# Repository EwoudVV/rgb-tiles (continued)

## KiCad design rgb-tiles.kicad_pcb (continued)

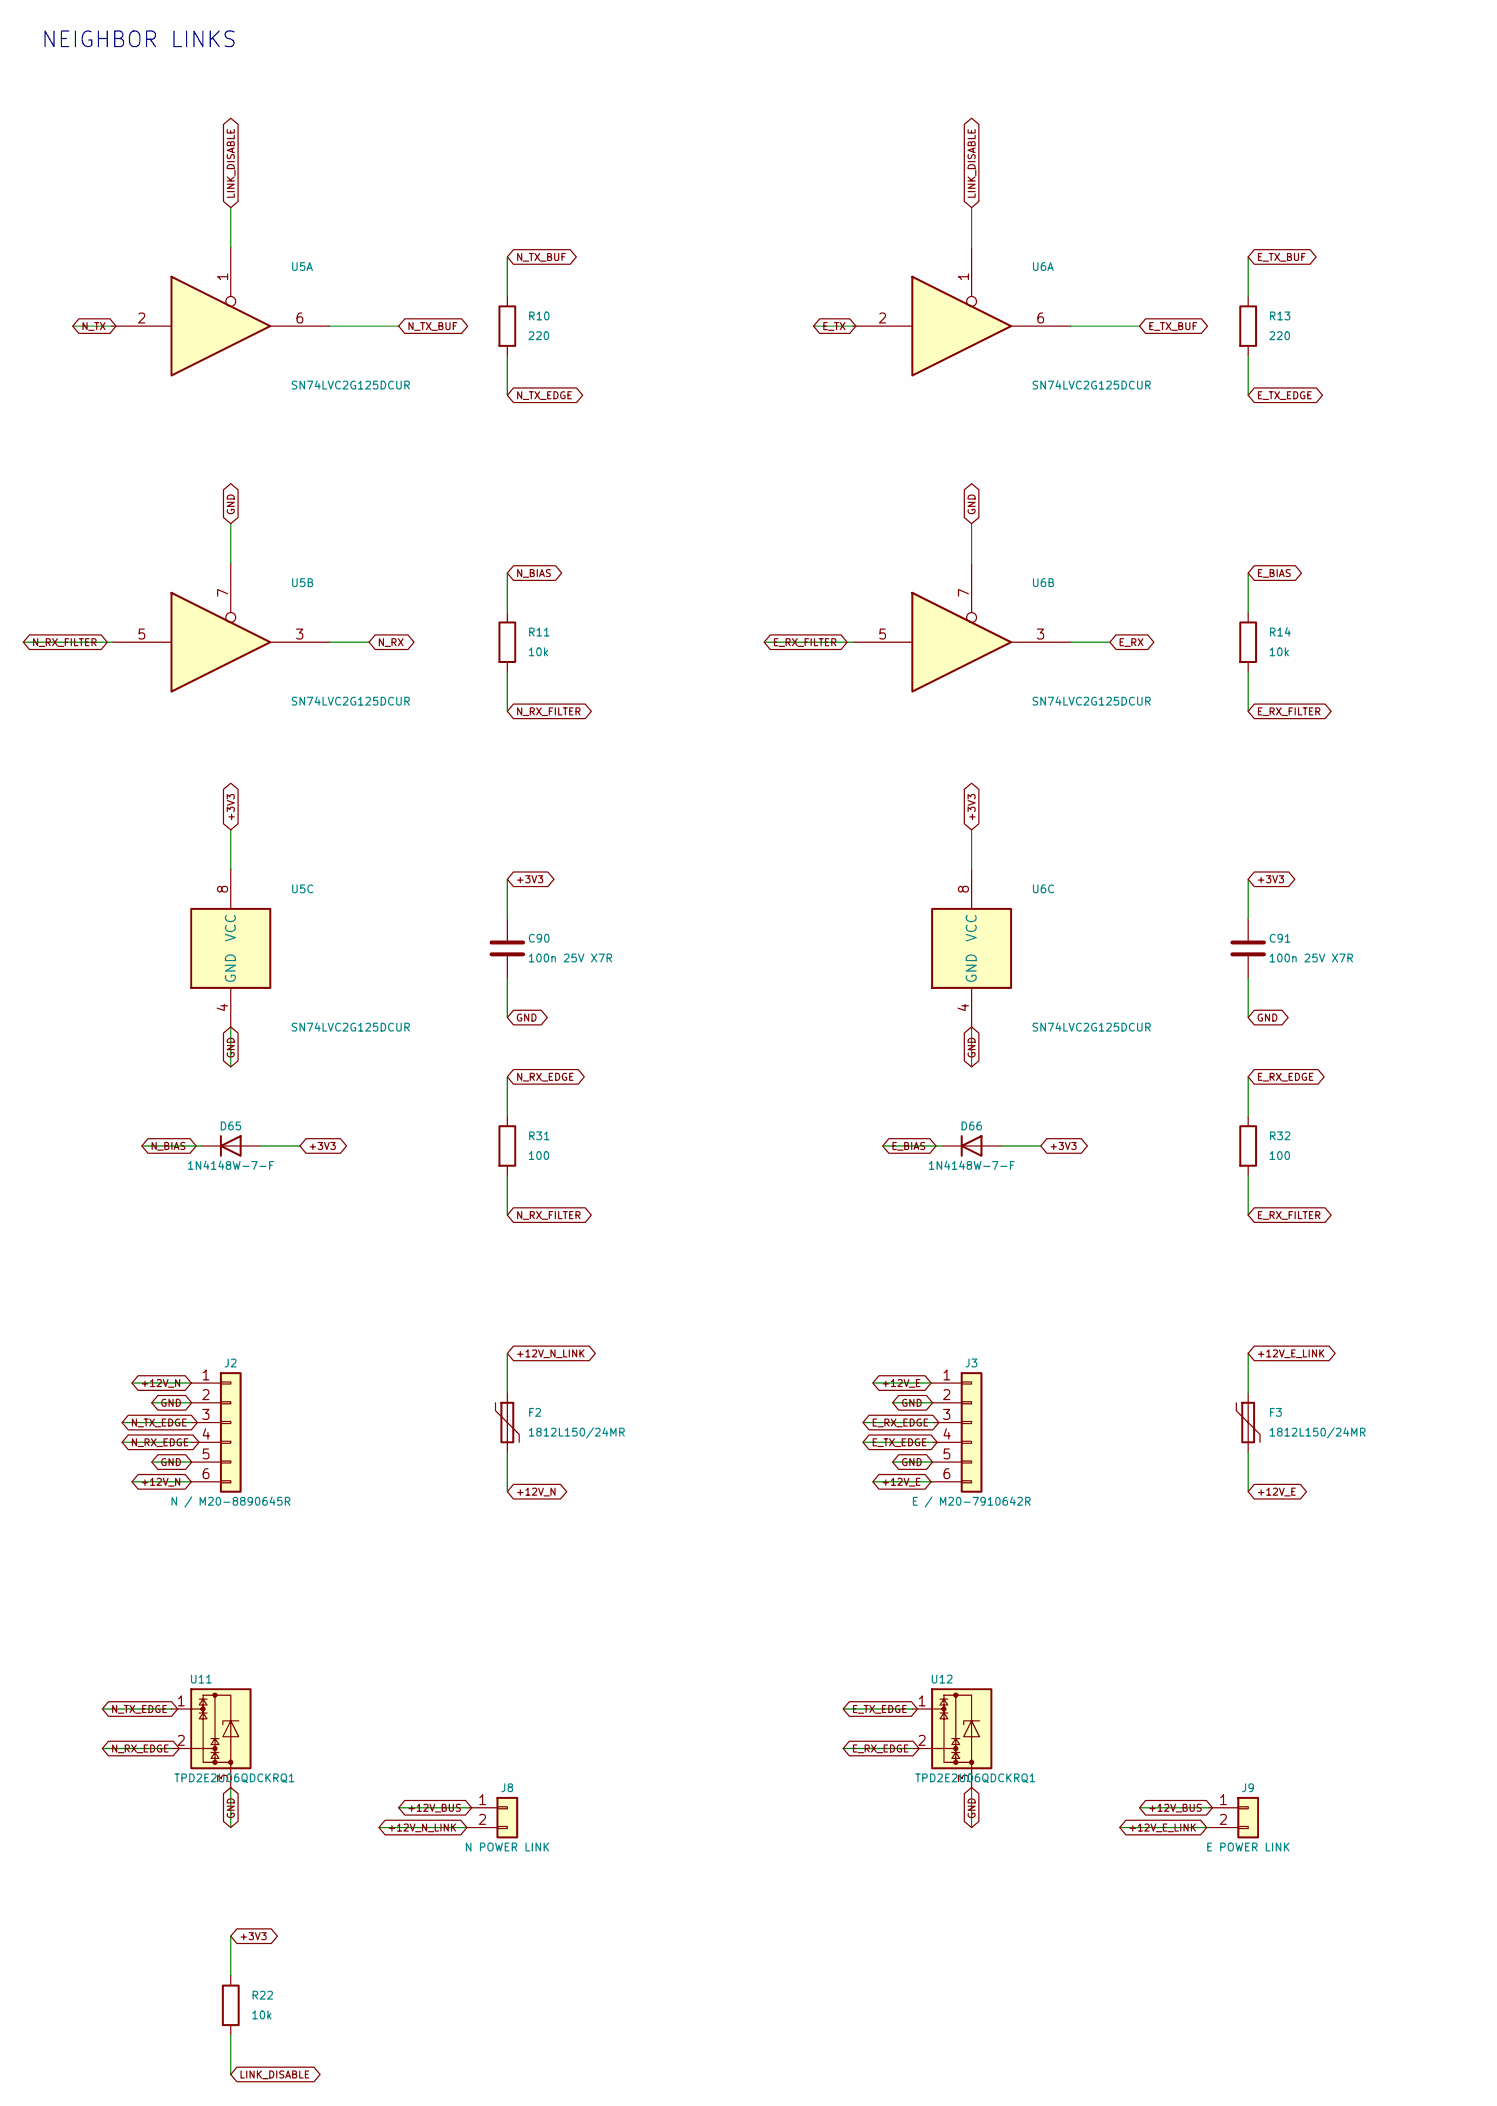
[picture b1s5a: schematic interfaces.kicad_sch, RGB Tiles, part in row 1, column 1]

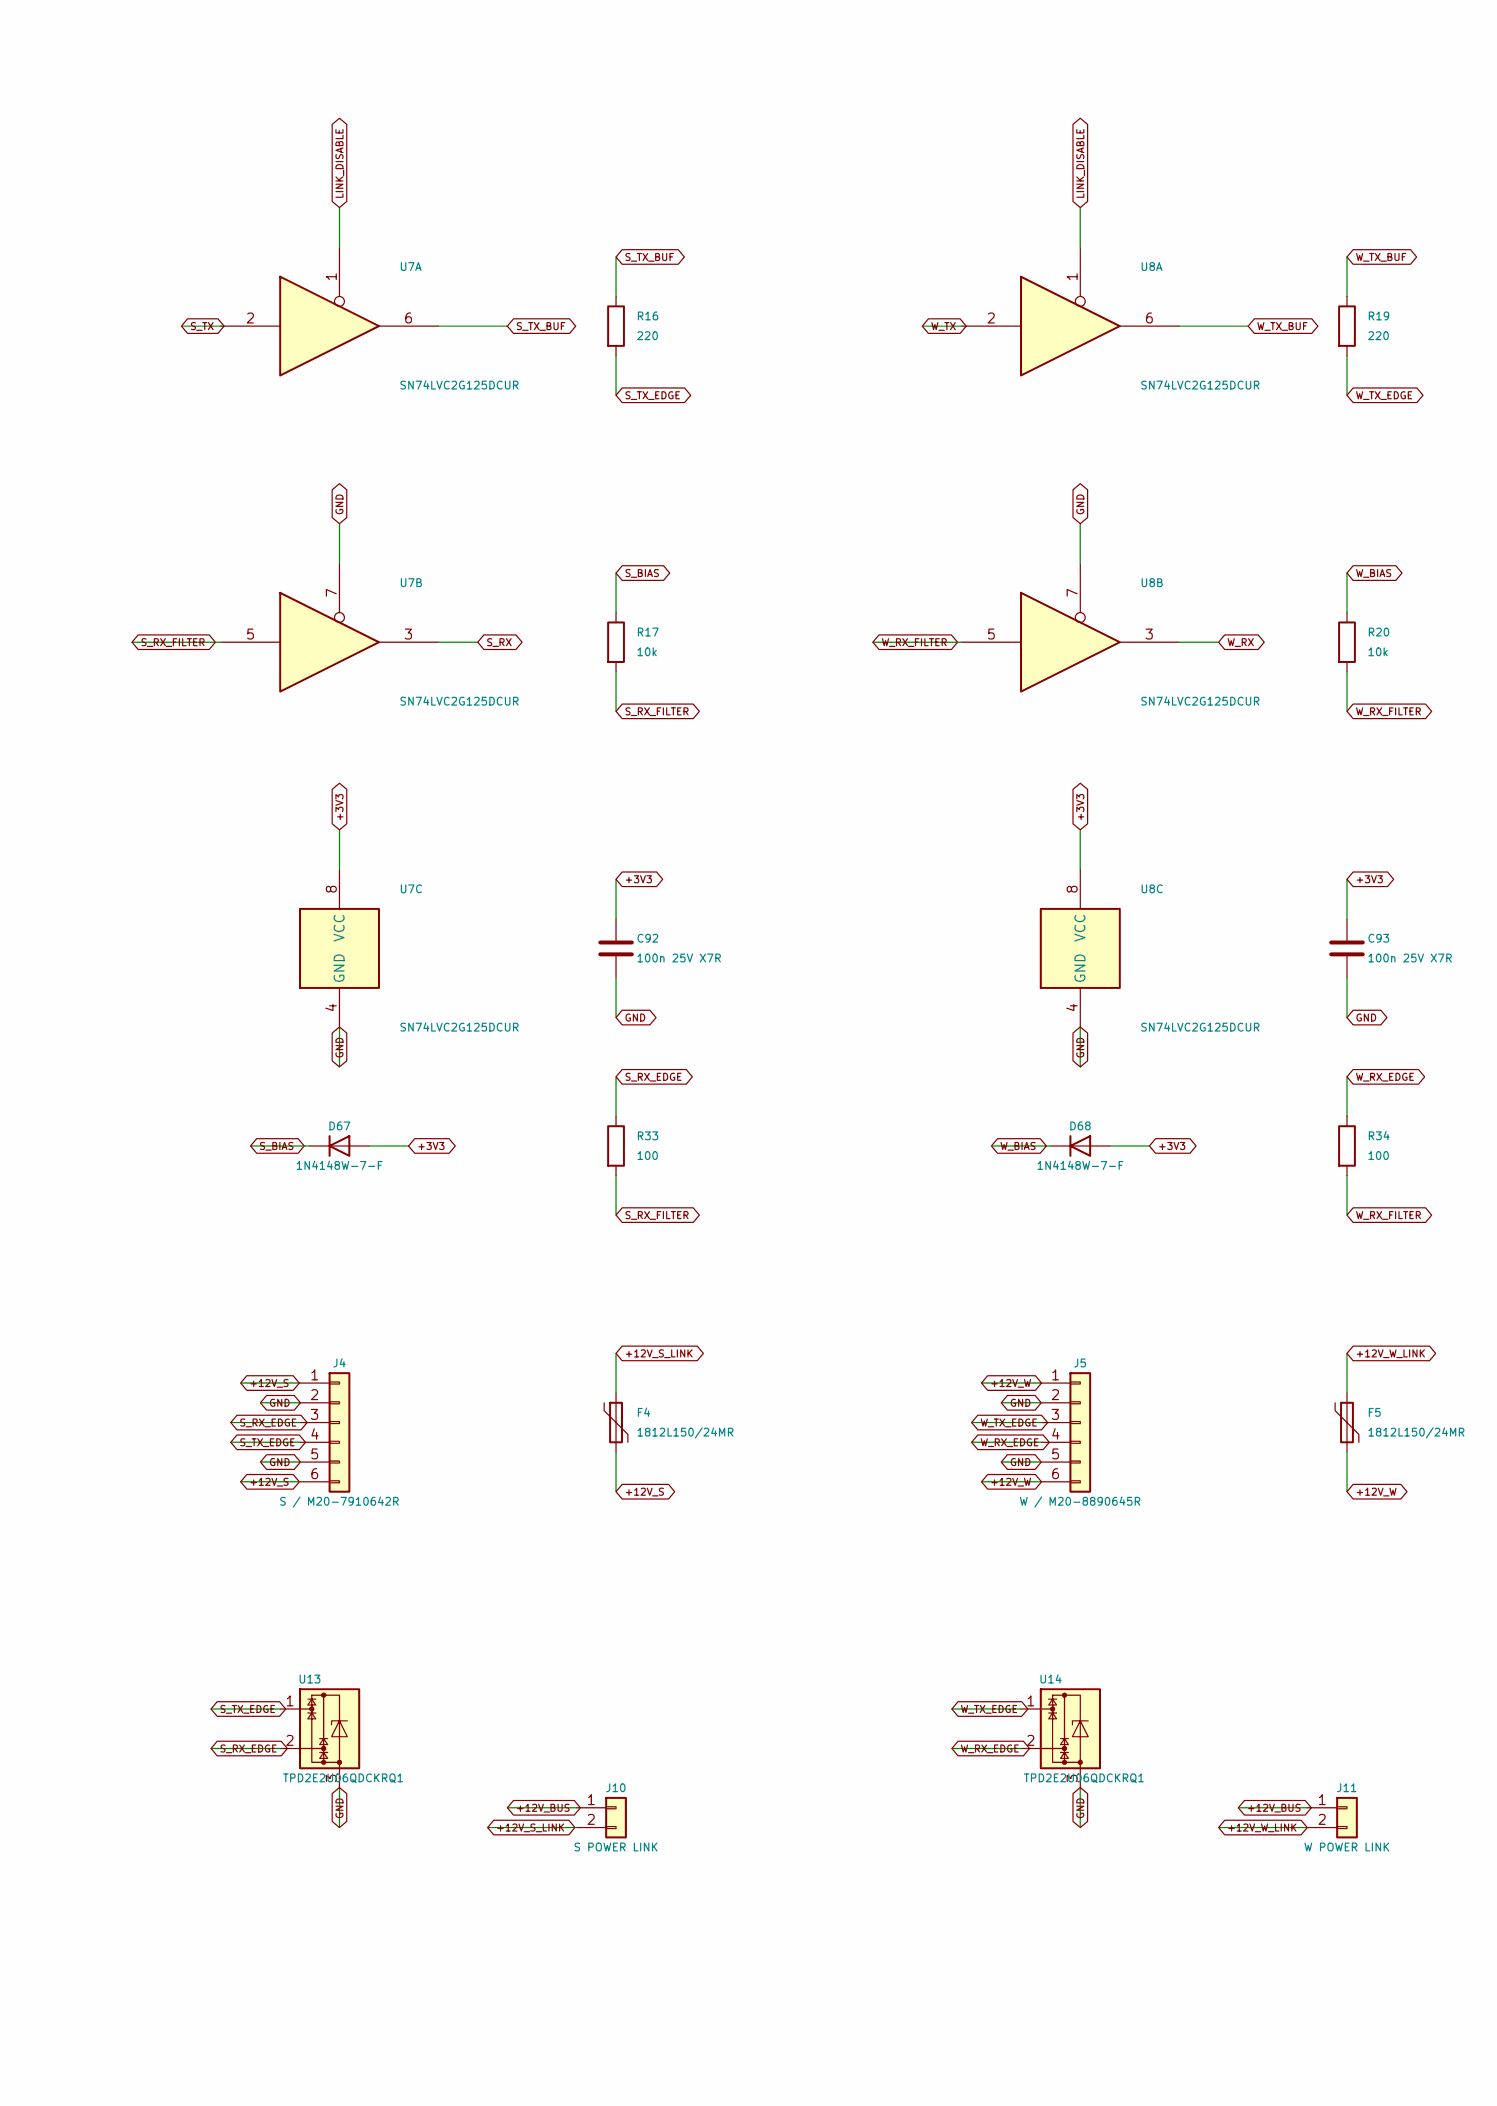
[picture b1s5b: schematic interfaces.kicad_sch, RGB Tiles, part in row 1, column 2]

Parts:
C90, C91, C92, C93: 100n 25V X7R; C_0603_1608Metric; MPN CL10B104KA8NNNC
D65, D66, D67, D68: 1N4148W-7-F; D_SOD-123; MPN 1N4148W-7-F
F2, F3, F4, F5: 1812L150/24MR; Fuse_1812_4532Metric; MPN 1812L150/24MR
J2: N / M20-8890645R; Harwin_M20-8890645R_1x06_RA_SMD; MPN M20-8890645R
J3: E / M20-7910642R; Harwin_M20-7910642R_1x06_RA_SMD; MPN M20-7910642R
J4: S / M20-7910642R; Harwin_M20-7910642R_1x06_RA_SMD; MPN M20-7910642R
J5: W / M20-8890645R; Harwin_M20-8890645R_1x06_RA_SMD; MPN M20-8890645R
J8: N POWER LINK; PinHeader_1x02_P2.54mm_Vertical; MPN A2541WV-2P
J9: E POWER LINK; PinHeader_1x02_P2.54mm_Vertical; MPN A2541WV-2P
J10: S POWER LINK; PinHeader_1x02_P2.54mm_Vertical; MPN A2541WV-2P
J11: W POWER LINK; PinHeader_1x02_P2.54mm_Vertical; MPN A2541WV-2P
R10, R13, R16, R19: 220; R_0603_1608Metric; Tolerance 1%; MPN RC0603FR-07220RL
R11, R14, R17, R20, R22: 10k; R_0603_1608Metric; Tolerance 1%; MPN RC0603FR-0710KL
R31, R32, R33, R34: 100; R_0603_1608Metric; Tolerance 1%; MPN RC0603FR-07100RL
U5, U6, U7, U8: SN74LVC2G125DCUR; VSSOP-8_2.3x2mm_P0.5mm; MPN SN74LVC2G125DCUR
U11, U12, U13, U14: TPD2E2U06QDCKRQ1; SOT-323_SC-70; MPN TPD2E2U06QDCKRQ1

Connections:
+3V3: C90.1, C91.1, C92.1, C93.1, D65.2 (A), D66.2 (A), D67.2 (A), D68.2 (A), R22.1, U5.8 (VCC), U6.8 (VCC), U7.8 (VCC), U8.8 (VCC); also elsewhere on the board
+12V_BUS: J8.1, J9.1, J10.1, J11.1; also elsewhere on the board
+12V_E: F3.2, J3.1, J3.6
+12V_E_LINK: F3.1, J9.2
+12V_N: F2.2, J2.1, J2.6
+12V_N_LINK: F2.1, J8.2
+12V_S: F4.2, J4.1, J4.6
+12V_S_LINK: F4.1, J10.2
+12V_W: F5.2, J5.1, J5.6
+12V_W_LINK: F5.1, J11.2
E_BIAS: D66.1 (K), R14.1
E_RX: U6.3; also elsewhere on the board
E_RX_EDGE: J3.3, R32.1, U12.2
E_RX_FILTER: R14.2, R32.2, U6.5
E_TX: U6.2; also elsewhere on the board
E_TX_BUF: R13.1, U6.6
E_TX_EDGE: J3.4, R13.2, U12.1
GND: C90.2, C91.2, C92.2, C93.2, J2.2, J2.5, J3.2, J3.5, J4.2, J4.5, J5.2, J5.5, U5.4 (GND), U5.7, U6.4 (GND), U6.7, U7.4 (GND), U7.7, U8.4 (GND), U8.7, U11.3, U12.3, U13.3, U14.3; also elsewhere on the board
LINK_DISABLE: R22.2, U5.1, U6.1, U7.1, U8.1; also elsewhere on the board
N_BIAS: D65.1 (K), R11.1
N_RX: U5.3; also elsewhere on the board
N_RX_EDGE: J2.4, R31.1, U11.2
N_RX_FILTER: R11.2, R31.2, U5.5
N_TX: U5.2; also elsewhere on the board
N_TX_BUF: R10.1, U5.6
N_TX_EDGE: J2.3, R10.2, U11.1
S_BIAS: D67.1 (K), R17.1
S_RX: U7.3; also elsewhere on the board
S_RX_EDGE: J4.3, R33.1, U13.2
S_RX_FILTER: R17.2, R33.2, U7.5
S_TX: U7.2; also elsewhere on the board
S_TX_BUF: R16.1, U7.6
S_TX_EDGE: J4.4, R16.2, U13.1
W_BIAS: D68.1 (K), R20.1
W_RX: U8.3; also elsewhere on the board
W_RX_EDGE: J5.4, R34.1, U14.2
W_RX_FILTER: R20.2, R34.2, U8.5
W_TX: U8.2; also elsewhere on the board
W_TX_BUF: R19.1, U8.6
W_TX_EDGE: J5.3, R19.2, U14.1

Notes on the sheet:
NEIGHBOR LINKS

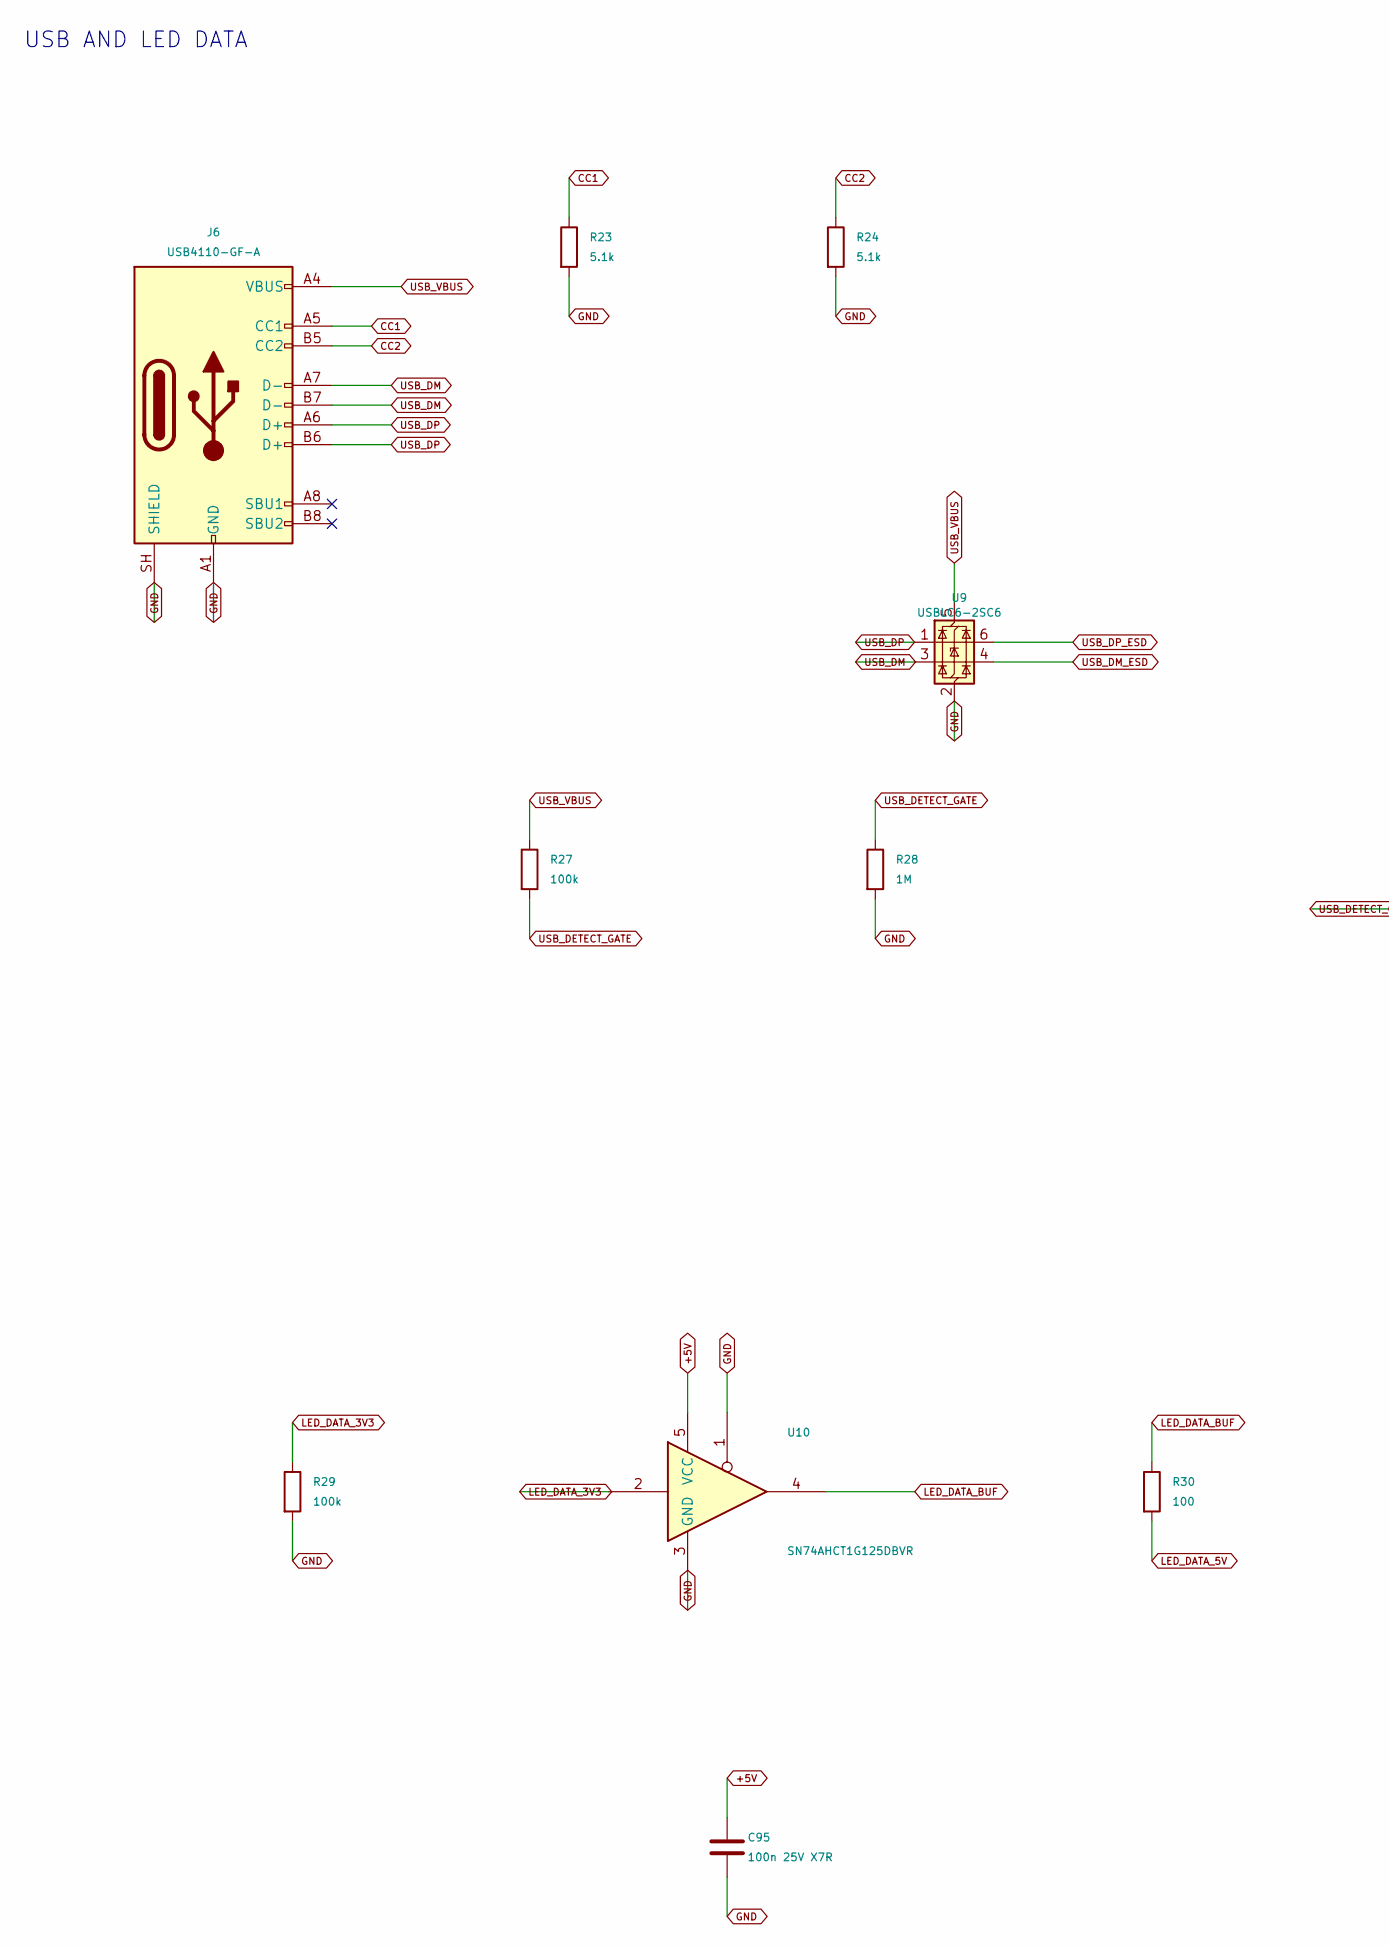
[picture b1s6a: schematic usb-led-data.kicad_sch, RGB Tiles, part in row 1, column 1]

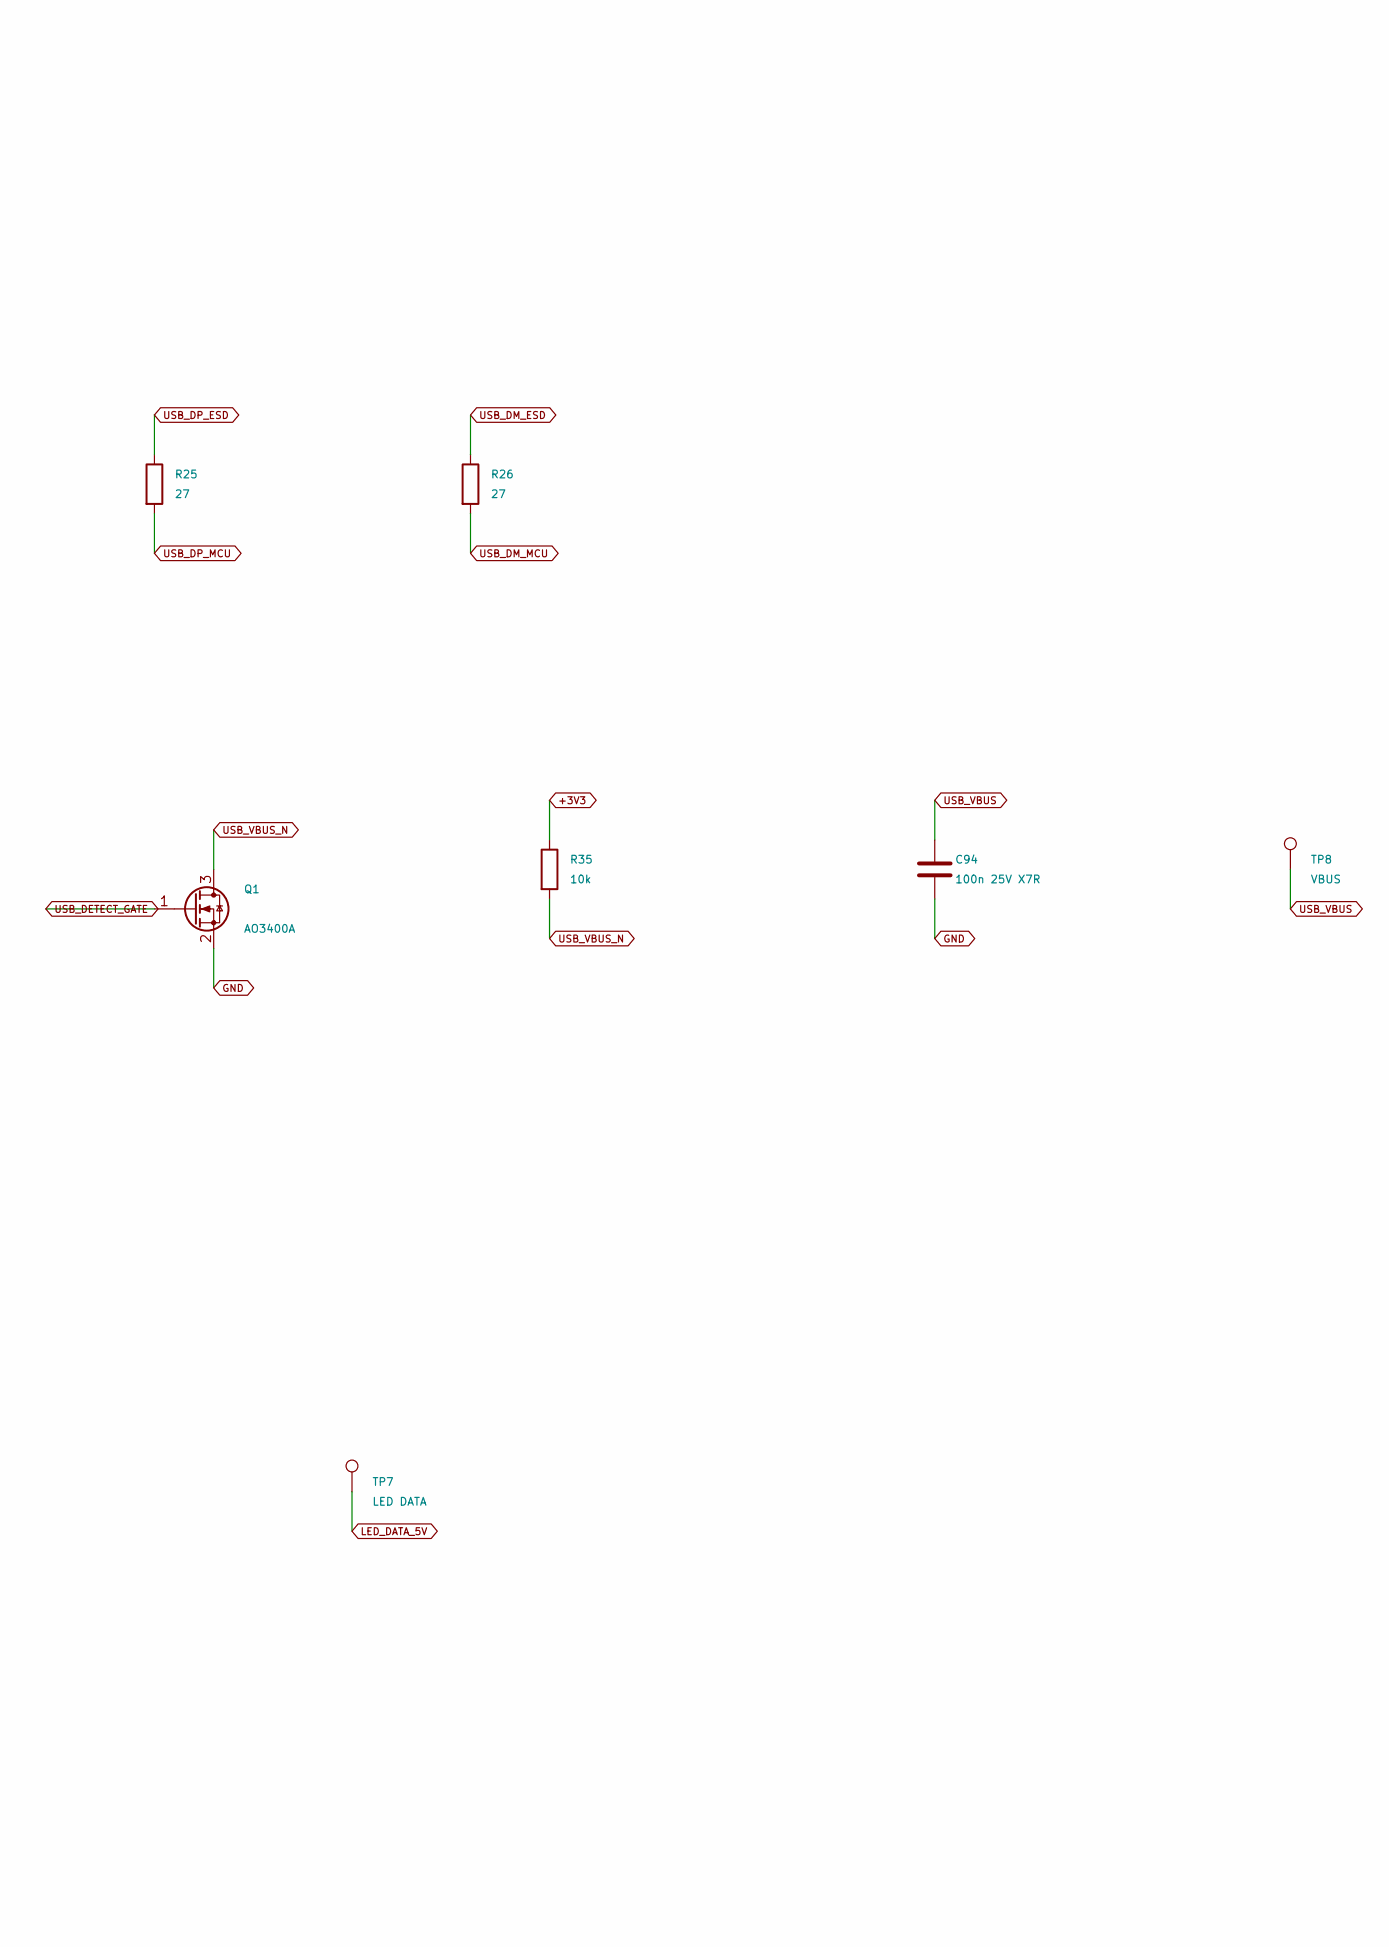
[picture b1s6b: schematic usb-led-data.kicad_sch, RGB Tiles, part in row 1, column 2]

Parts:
C94, C95: 100n 25V X7R; C_0603_1608Metric; MPN CL10B104KA8NNNC
J6: USB4110-GF-A; USB_C_Receptacle_GCT_USB4110; MPN USB4110-GF-A
Q1: AO3400A; SOT-23; MPN AO3400A
R23, R24: 5.1k; R_0603_1608Metric; Tolerance 1%; MPN RC0603FR-075K1L
R25, R26: 27; R_0603_1608Metric; Tolerance 1%; MPN RC0603FR-0727RL
R27, R29: 100k; R_0603_1608Metric; Tolerance 1%; MPN RC0603FR-07100KL
R28: 1M; R_0603_1608Metric; Tolerance 1%; MPN RC0603FR-071ML
R30: 100; R_0603_1608Metric; Tolerance 1%; MPN RC0603FR-07100RL
R35: 10k; R_0603_1608Metric; Tolerance 1%; MPN RC0603FR-0710KL
TP7: LED DATA; TestPoint_Pad_D1.5mm
TP8: VBUS; TestPoint_Pad_D1.5mm
U9: USBLC6-2SC6; SOT-23-6; MPN USBLC6-2SC6
U10: SN74AHCT1G125DBVR; SOT-23-5; MPN SN74AHCT1G125DBVR

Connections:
+3V3: R35.1; also elsewhere on the board
+5V: C95.1, U10.5 (VCC); also elsewhere on the board
CC1: J6.A5 (CC1), R23.1
CC2: J6.B5 (CC2), R24.1
GND: C94.2, C95.2, J6.A1 (GND), J6.A12 (GND), J6.B1 (GND), J6.B12 (GND), J6.SH (SHIELD), Q1.2 (S), R23.2, R24.2, R28.2, R29.2, U9.2 (GND), U10.1, U10.3 (GND); also elsewhere on the board
LED_DATA_3V3: R29.1, U10.2; also elsewhere on the board
LED_DATA_5V: R30.2, TP7.1; also elsewhere on the board
LED_DATA_BUF: R30.1, U10.4
USB_DETECT_GATE: Q1.1 (G), R27.2, R28.1
USB_DM: J6.A7 (D-), J6.B7 (D-), U9.3 (I/O2)
USB_DM_ESD: R26.1, U9.4 (I/O2)
USB_DM_MCU: R26.2; also elsewhere on the board
USB_DP: J6.A6 (D+), J6.B6 (D+), U9.1 (I/O1)
USB_DP_ESD: R25.1, U9.6 (I/O1)
USB_DP_MCU: R25.2; also elsewhere on the board
USB_VBUS: C94.1, J6.A4 (VBUS), J6.A9 (VBUS), J6.B4 (VBUS), J6.B9 (VBUS), R27.1, TP8.1, U9.5 (VBUS)
USB_VBUS_N: Q1.3 (D), R35.2; also elsewhere on the board

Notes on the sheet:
USB AND LED DATA

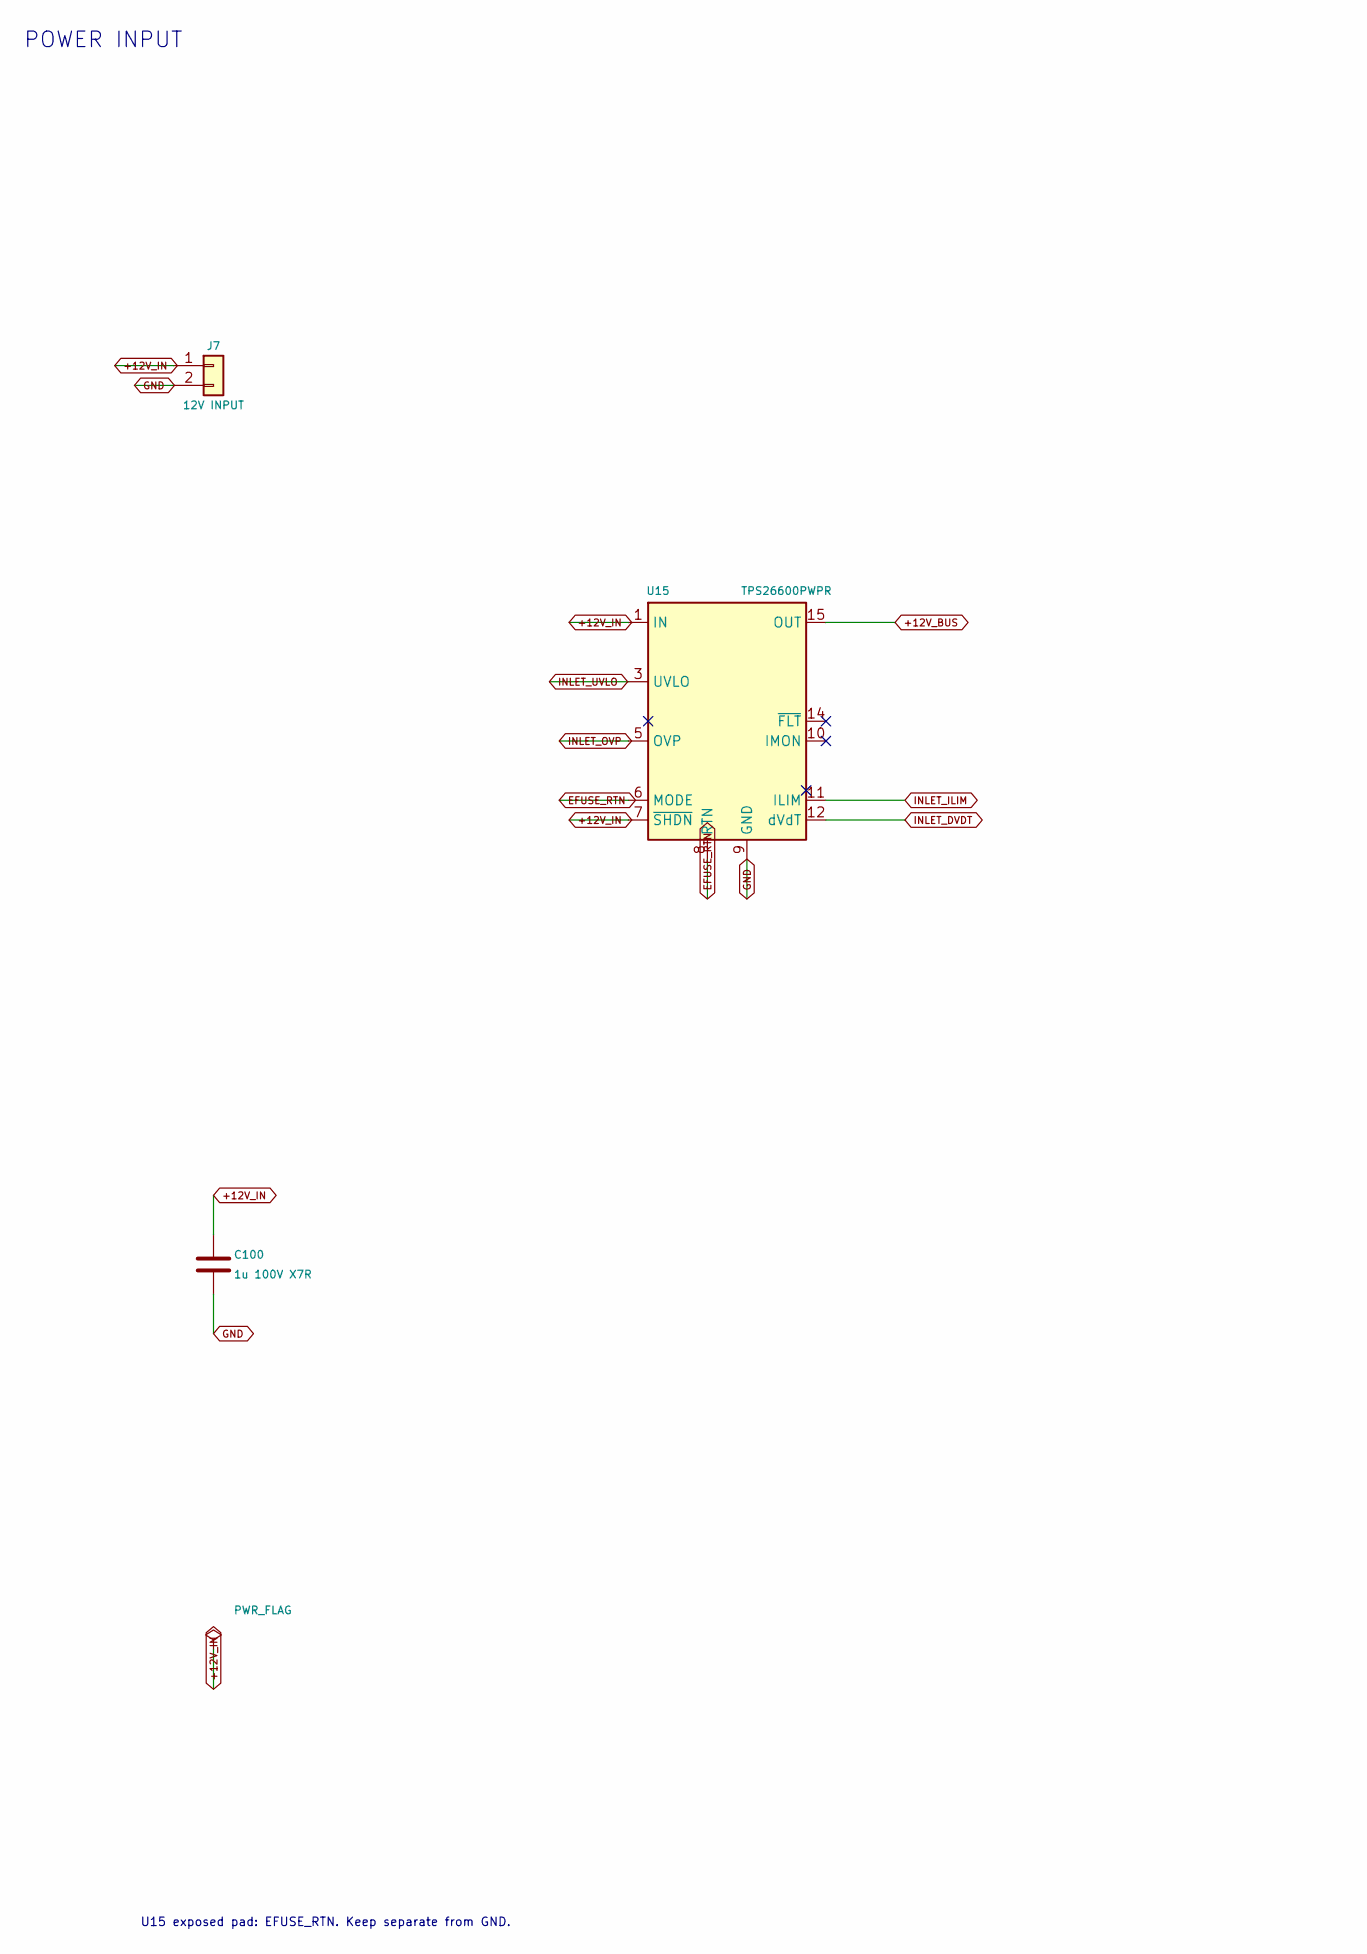
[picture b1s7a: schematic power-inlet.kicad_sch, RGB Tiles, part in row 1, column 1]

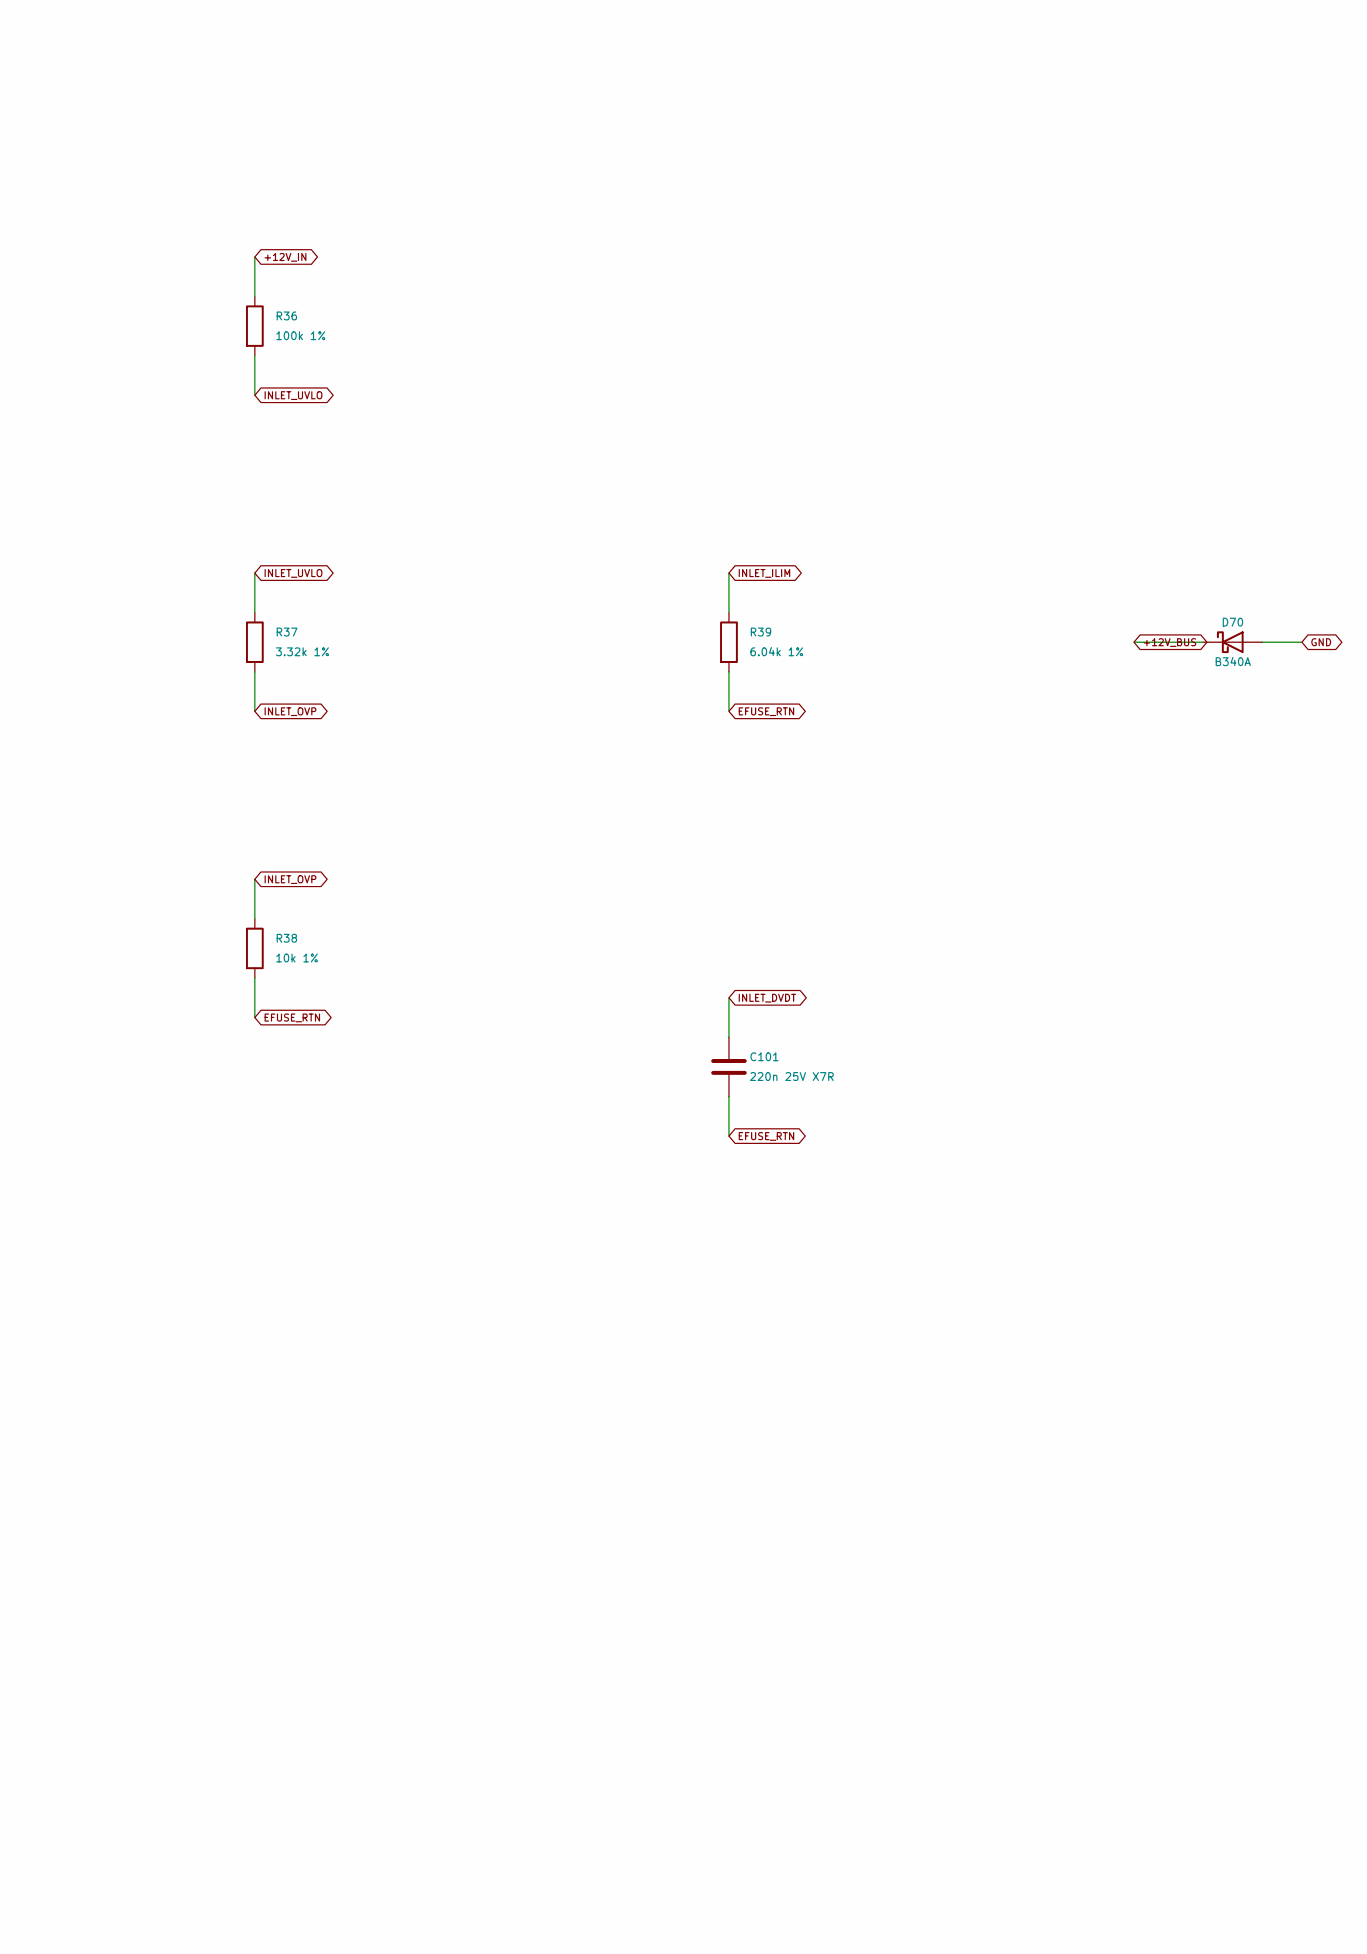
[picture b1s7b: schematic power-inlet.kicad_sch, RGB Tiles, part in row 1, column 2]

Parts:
C100: 1u 100V X7R; C_1206_3216Metric; MPN C1206C105K1RACTU
C101: 220n 25V X7R; C_0603_1608Metric; MPN C0603C224K3RACTU
D70: B340A; D_SMA; MPN B340A-13-F
J7: 12V INPUT; TerminalBlock_Phoenix_MKDS-1,5-2-5.08_1x02_P5.08mm_Horizont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; MPN 1715721
R36: 100k 1%; R_0603_1608Metric; Tolerance 1%; MPN RC0603FR-07100KL
R37: 3.32k 1%; R_0603_1608Metric; Tolerance 1%; MPN RC0603FR-073K32L
R38: 10k 1%; R_0603_1608Metric; Tolerance 1%; MPN RC0603FR-0710KL
R39: 6.04k 1%; R_0603_1608Metric; Tolerance 1%; MPN RC0603FR-076K04L
U15: TPS26600PWPR; HTSSOP16_EP_4.4x5_P0.65_Vias0.3; MPN TPS26600PWPR

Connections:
+12V_BUS: D70.1 (K), U15.15 (OUT), U15.16 (OUT); also elsewhere on the board
+12V_IN: C100.1, J7.1, R36.1, U15.1 (IN), U15.2 (IN), U15.7 (~SHDN)
EFUSE_RTN: C101.2, R38.2, R39.2, U15.6 (MODE), U15.8 (RTN), U15.17 (RTN)
GND: C100.2, D70.2 (A), J7.2, U15.9 (GND); also elsewhere on the board
INLET_DVDT: C101.1, U15.12 (dVdT)
INLET_ILIM: R39.1, U15.11 (ILIM)
INLET_OVP: R37.2, R38.1, U15.5 (OVP)
INLET_UVLO: R36.2, R37.1, U15.3 (UVLO)

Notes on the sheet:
POWER INPUT
U15 exposed pad: EFUSE_RTN. Keep separate from GND.
